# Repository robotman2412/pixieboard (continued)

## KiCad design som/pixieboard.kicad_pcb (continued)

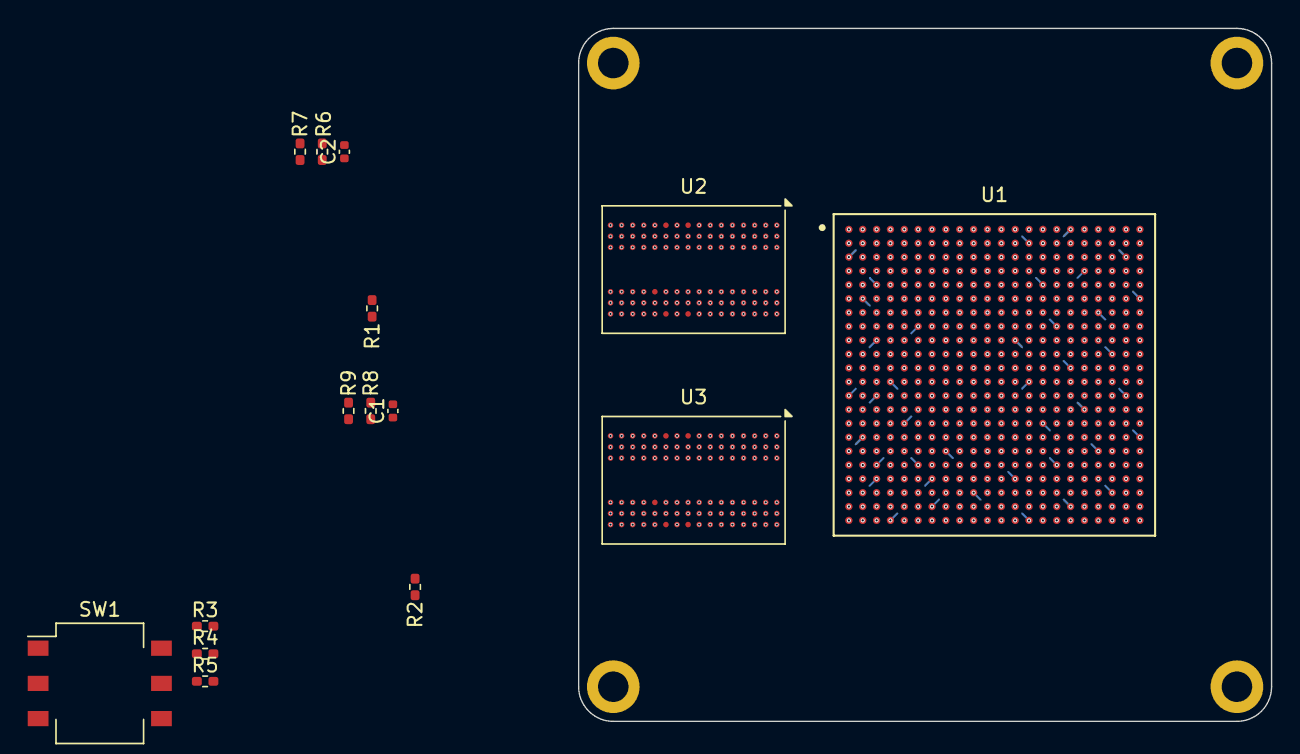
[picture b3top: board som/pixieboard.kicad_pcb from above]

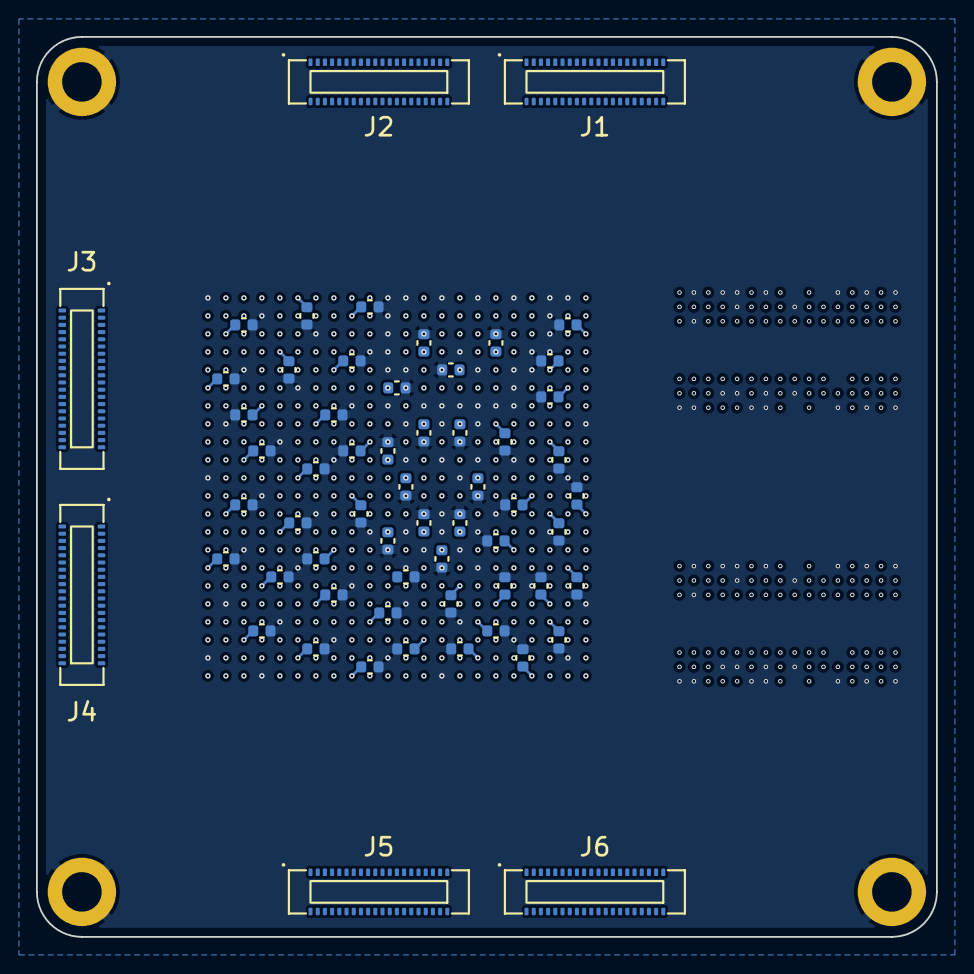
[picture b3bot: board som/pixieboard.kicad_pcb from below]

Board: 8 copper layers, 50.0 x 50.0 mm, 79 parts (60 on the bottom side), 89 nets.

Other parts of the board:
R6, R7, R8, R9: 10k; R_0402_1005Metric_Pad0.72x0.64mm_HandSolder

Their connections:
+1V35: R6.1, R8.1; also elsewhere on the board
GND: R7.2, R9.2; also elsewhere on the board
unnamed: R6.2, R7.1
unnamed: R8.2, R9.1

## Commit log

2024-04-05 lmfao l
2024-04-06 Completed DDR3L routing
2024-04-07 Mezz Power Tweak Ok
2024-04-07 o.k.
2024-04-08 Le DDR3 control traces
2024-04-09 O.K. lettuce try again
2024-04-09 It uses only 3 layers now
2024-04-19 DDR3 (again)
2024-05-12 Remove footprint info cache from git
2024-07-22 I really should commit when I make it and not a month later
2024-08-15 Fix the capacitor problem
2024-08-16 Place some caps
2024-10-01 Work on GTP and power supplies for it
2024-10-05 GTP stuff
2024-10-06 A little 155 pin I/O breakout
2025-06-16 Convert to KiCad 9 project
2025-06-16 Change paths to be project-relative
2025-06-16 Add power test project that is stripped of FPGA and DDR3L.
2025-06-16 Migrate evey power wire off layers in3-in6
2025-06-16 Remove layers in3-in6 from powertest pcb
2025-06-16 Add large pads for connection to a synthetic load
2025-06-16 Add missing dimension
2025-06-16 Add revision text
2025-06-16 Basic carrier board stub
2025-06-17 Experiment with how I want to place some I/O on the basic carrier
2025-06-17 Make power traces on SOM thicker, more experimentallingification with carrier I/O layout
2025-06-17 Fix USB-C connector symbol and footprint
2025-06-17 Fix 3D models
2025-07-10 Some more work on the carrier
